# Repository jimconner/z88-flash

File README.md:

# z88-flash

An open-source expansion card for the Cambridge Z88 which can be configured as 512KB RAM, 1MB RAM or 1MB Flash.

This work is based upon the Z88 connector design shared by XavSnap at [SinclairZXWorld Z88 Forum](https://sinclairzxworld.com/viewtopic.php?f=24&t=4431) - Thank you XavSnap!

I found that I had 4 x AM29F080 (1MBit * 8) Flash memory chips on a stick which came out of a Cisco router in the 1990s. This chip is reported to be compatbile with the Cambridge Z88, so as a fun project I decided that I'd use one of the cheap PCB manufacturing services and make myself some Flash expansion cards.

The first revision of this board was only designed to support 1MB Flash, but upon receiving the first set of PCBs, it was discovered that XavSnap's design was using 1.27mm pin pitch whereas the Z88 uses 1.25. During the redesign support was added for using either one or two 512KB SRAM chips instead of Flash. The PCB can now support either 1x1MB Flash, 1x 512KB SRAM or 2x512KB SRAM (74139 required)

* To use with 512KB SRAM (HY628400A or AS6C4008), populate C2 and U2 and short the 512K solder jumper. (C2 is not populated in the photo below because I was mid-way through building)

* To use with 1MB Flash populate only U1(AM29F080) and C1(100nF)
* To use with 1MB SRAM populate C2 & C3(100nF), U2 & U3(HY628400A or AS6C4008) and U4(74139)

* The SRAM configurations of the board and hand-solderable, for for the flash chip it's a lot easier to use solder paste and hot air.
* You may optionally populate R1 and D1 with a 220Ohm resistor and an LED to gain a 'Writing' status LED.

If you're looking for a one-off I'd recommend purchasing Rakewell's reasonably priced bare PCB, but I was more looking for a fun project. I also wanted a solder paste stencil for hot air reflow soldering which Rakewell do not provide. A batch of 5 PCBs from Shenzen, with gold plating, solder stencil and the cheapest shipping cost a little over £30 (in 2023).

If you do decide to make this, do not underestimate the importance of the plastic case which holds the card. I struggled initially with 3D Printed cases, but discovered that the slighets warp in the print, or lack of pressure holding the card tightly in place causes a lot of problems. I'd recommend disassembling and reusing an existing card case for your first attempt, and wrapping a single layer of tape around it to ensure that the connector edge is clamped to the back shell firmly. Only once you're confident that a PCB is working correclty should you think about putting it in a printed case.

Unfortunately the slik-screen on the PCB doesn't clearly show the pin1 markings, so check the 3D board picture below, the photos above open the PCB design with KiCAD to be absolutely certain you've got it correct. The Flash chip has pin1 facing towards the edge connector, the ram chips have pin1 at the edge of the PCB and the 74139 is the same orientation as the RAM chips.

* With this much memory, you can have every piece of software ever written for the Z88 both stored on Flash, and running in RAM... with enough space remaining to do it all over again.

I've tested all three configurations of this design with my Z88 successfully, but haven't tested adding a status LED - I don't anticipate any problems with that - I just didn't have any surface mount LEDs to use.

I found the component stencil and footprint for the AM29F080 as free downloads at [Ultra Librarian](https://www.ultralibrarian.com/) - I have not included them in this archive as they are almost certianly not licensed for redistribution, but you should be able to sign up for a free account and download a copy.

The 3D printed card case availabile from Thingverse does not quite fit the standard z88 card design, and you need to sand down the chamfered corners on the PCBs a little to make it fit - With a pre-made case it'll fit fine. It has been noted that the placement of the LED in the centre of the board makes adding a label to the card problematic, so if you're planning on making any refinements to the board, that could be worthwhile tweak.

If you're just looking to order PCBs without making any modifications then the `Z88_1MB_Flash.zip` file contains all of the gerbers and drill files you need to upload. You should just need to upload the file and hit 'order-pcb' at your preferred manufacturer.

This project is released as an Open Source Hardware offering. Do with it whatever you will, but don't blame me if things go wrong.

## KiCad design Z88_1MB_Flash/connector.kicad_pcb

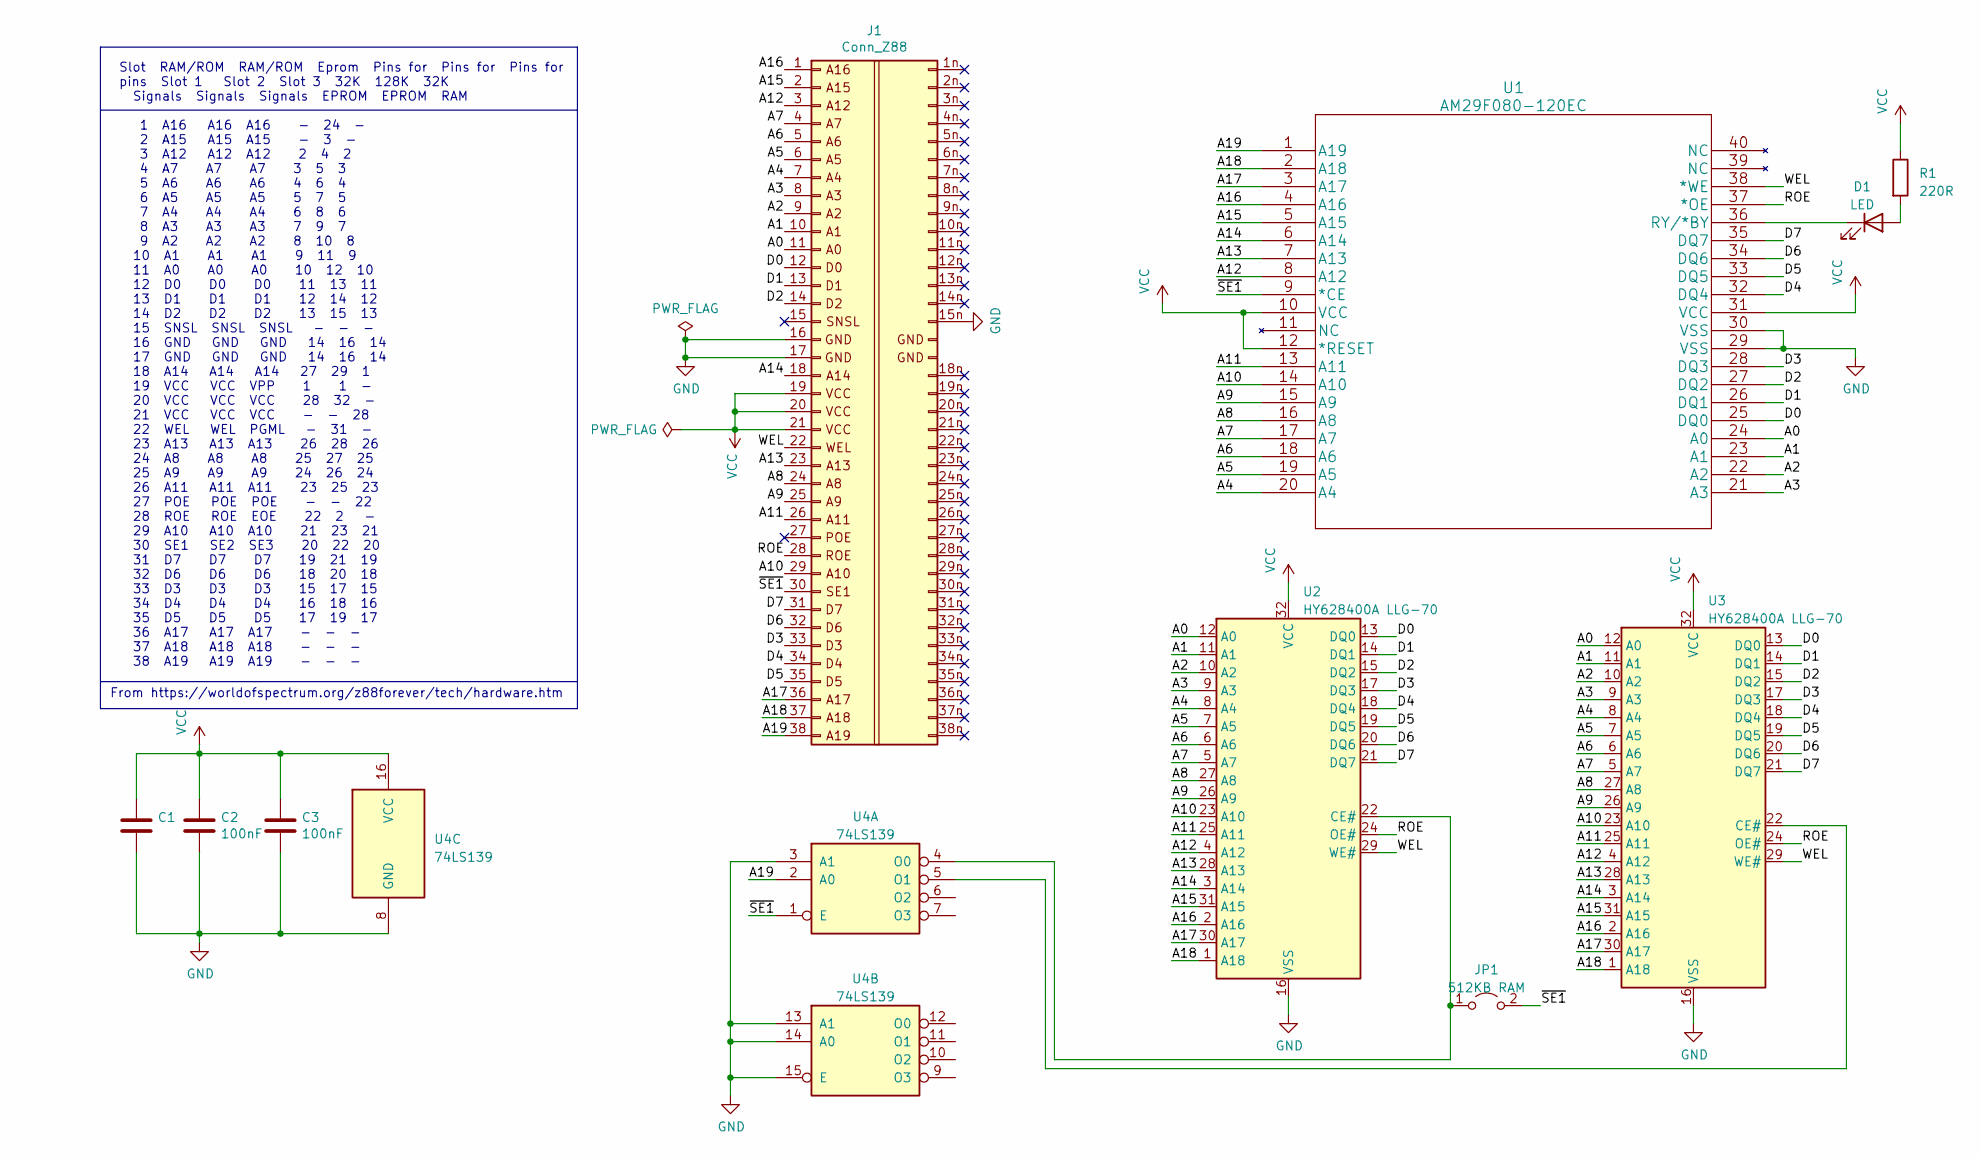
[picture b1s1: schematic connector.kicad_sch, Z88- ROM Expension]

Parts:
C1, C2, C3: 100nF; C_1206_3216Metric
D1: LED; LED_1206_3216Metric
J1: Conn_Z88; Z88_connector
JP1: 512KB RAM; SolderJumper-2_P1.3mm_Open_Pad1.0x1.5mm
R1: 220R; R_0805_2012Metric_Pad1.20x1.40mm_HandSolder
U1: AM29F080-120EC; TSOP-I-40_18.4x10mm_P0.5mm
U2, U3: HY628400A LLG-70; SSOP-32_11.305x20.495mm_P1.27mm
U4: 74LS139; SO-16_3.9x9.9mm_P1.27mm

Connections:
/A0: J1.11, U1.24 (A0), U2.12 (A0), U3.12 (A0)
/A1: J1.10, U1.23 (A1), U2.11 (A1), U3.11 (A1)
/A2: J1.9, U1.22 (A2), U2.10 (A2), U3.10 (A2)
/A3: J1.8, U1.21 (A3), U2.9 (A3), U3.9 (A3)
/A4: J1.7, U1.20 (A4), U2.8 (A4), U3.8 (A4)
/A5: J1.6, U1.19 (A5), U2.7 (A5), U3.7 (A5)
/A6: J1.5, U1.18 (A6), U2.6 (A6), U3.6 (A6)
/A7: J1.4, U1.17 (A7), U2.5 (A7), U3.5 (A7)
/A8: J1.24, U1.16 (A8), U2.27 (A8), U3.27 (A8)
/A9: J1.25, U1.15 (A9), U2.26 (A9), U3.26 (A9)
/A10: J1.29, U1.14 (A10), U2.23 (A10), U3.23 (A10)
/A11: J1.26, U1.13 (A11), U2.25 (A11), U3.25 (A11)
/A12: J1.3, U1.8 (A12), U2.4 (A12), U3.4 (A12)
/A13: J1.23, U1.7 (A13), U2.28 (A13), U3.28 (A13)
/A14: J1.18, U1.6 (A14), U2.3 (A14), U3.3 (A14)
/A15: J1.2, U1.5 (A15), U2.31 (A15), U3.31 (A15)
/A16: J1.1, U1.4 (A16), U2.2 (A16), U3.2 (A16)
/A17: J1.36, U1.3 (A17), U2.30 (A17), U3.30 (A17)
/A18: J1.37, U1.2 (A18), U2.1 (A18), U3.1 (A18)
/A19: J1.38, U1.1 (A19), U4.2 (A0)
/D0: J1.12, U1.25 (DQ0), U2.13 (DQ0), U3.13 (DQ0)
/D1: J1.13, U1.26 (DQ1), U2.14 (DQ1), U3.14 (DQ1)
/D2: J1.14, U1.27 (DQ2), U2.15 (DQ2), U3.15 (DQ2)
/D3: J1.33, U1.28 (DQ3), U2.17 (DQ3), U3.17 (DQ3)
/D4: J1.34, U1.32 (DQ4), U2.18 (DQ4), U3.18 (DQ4)
/D5: J1.35, U1.33 (DQ5), U2.19 (DQ5), U3.19 (DQ5)
/D6: J1.32, U1.34 (DQ6), U2.20 (DQ6), U3.20 (DQ6)
/D7: J1.31, U1.35 (DQ7), U2.21 (DQ7), U3.21 (DQ7)
/ROE: J1.28, U1.37 (*OE), U2.24 (OE#), U3.24 (OE#)
/WEL: J1.22, U1.38 (*WE), U2.29 (WE#), U3.29 (WE#)
/~SE1: J1.30, JP1.2 (B), U1.9 (*CE), U4.1 (E); also elsewhere on the board
GND: C1.2, C2.2, C3.2, J1.15n (Pin_53), J1.16 (GND), J1.17 (GND), U1.29 (VSS), U1.30 (VSS), U2.16 (VSS), U3.16 (VSS), U4.3 (A1), U4.8 (GND), U4.13 (A1), U4.14 (A0), U4.15 (E)
unnamed: D1.2 (A), R1.2
unnamed: D1.1 (K), U1.36 (RY/*BY)
unnamed 34: JP1.1 (A), U2.22 (CE#), U4.4 (O0); also elsewhere on the board
unnamed: U3.22 (CE#), U4.5 (O1)
VCC: C1.1, C2.1, C3.1, J1.19, J1.20, J1.21, R1.1, U1.10 (VCC), U1.12 (*RESET), U1.31 (VCC), U2.32 (VCC), U3.32 (VCC), U4.16 (VCC)

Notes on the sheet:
From https://worldofspectrum.org/z88forever/tech/hardware.htm
Slot RAM/ROM RAM/ROM Eprom Pins for Pins for Pins for pins Slot 1 Slot 2 Slot 3 32K 128K 32K Signals Signals Signals EPROM EPROM RAM 1 A16 A16 A16 - 24 - 2 A15 A15 A15 - 3 - 3 A12 A12 A12 2 4 2 4 A7 A7 A7 3 5 3 5 A6 A6 A6 4 6 4 6 A5 A5 A5 5 7 5 7 A4 A4 A4 6 8 6 8 A3 A3 A3 7 9 7 9 A2 A2 A2 8 10 8 10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

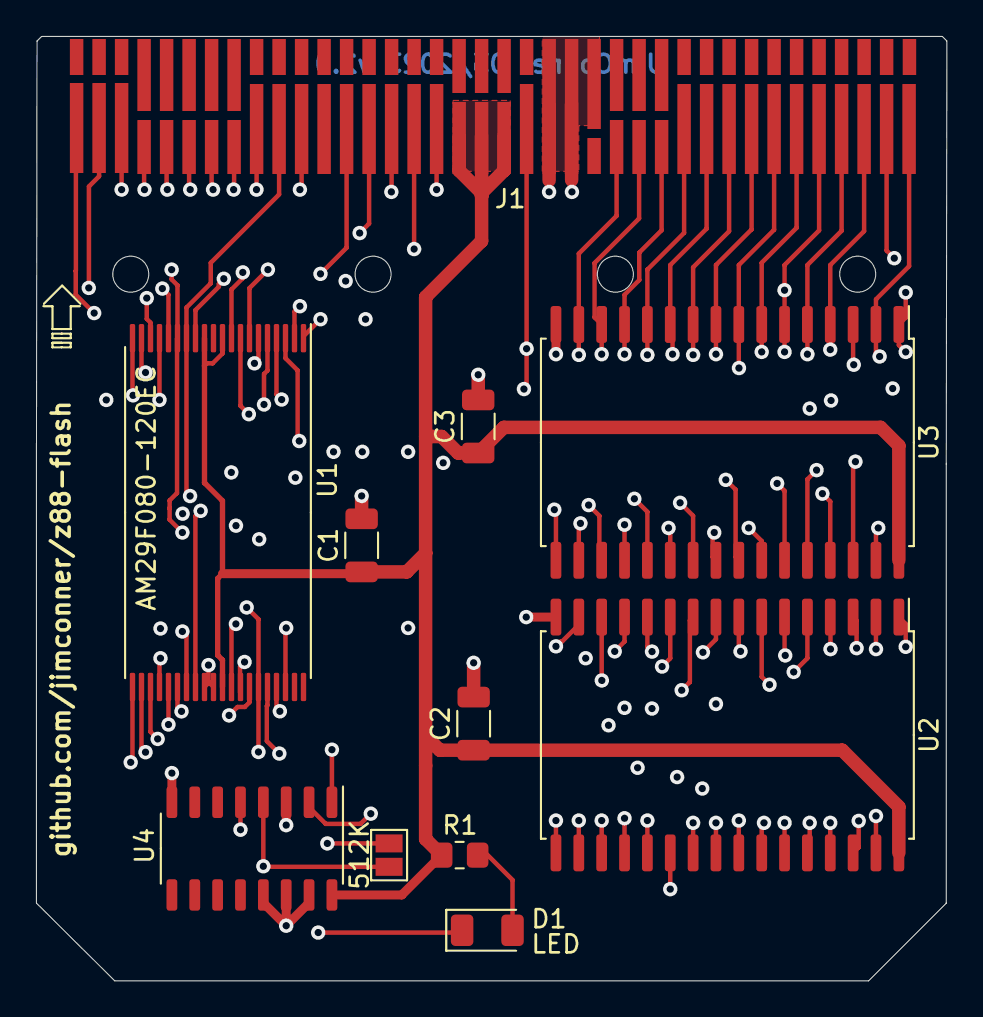
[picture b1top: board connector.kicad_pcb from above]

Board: 4 copper layers, 50.6 x 52.5 mm, 11 parts (0 on the bottom side), 37 nets.

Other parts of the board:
512K: 512KB RAM; SolderJumper-2_P1.3mm_Open_Pad1.0x1.5mm

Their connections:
/~SE1: 512K.2 (B); also elsewhere on the board
unnamed 34: 512K.1 (A); also elsewhere on the board

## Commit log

2023-03-10 Version of files sent to manufacturing.
2023-03-21 Correct pitch on Z88_connector.
    Pads now spaced on 1.25mm instead of 1.27mm spacing.
    Pad sizes changed to match the genuine Cambridge cartridge I have.
    Sizes nicely in convienent 2m,3mm, 4mm sizing with 0.5mm gap.
2023-03-25 Add support for using 2 x 512KB SRAM chips instead of 1MB Flash.
    The board can now be used either as a 1MB Flash store, 512KB RAM or 1MB
    RAM.
2023-04-07 All configurations tested successfully - docs update.
